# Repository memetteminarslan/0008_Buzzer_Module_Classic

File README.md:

# 0008_Buzzer_Module_Classic
You are seeing a large number of widely used Buzzer modules in electronic development kits. More information coming soon...

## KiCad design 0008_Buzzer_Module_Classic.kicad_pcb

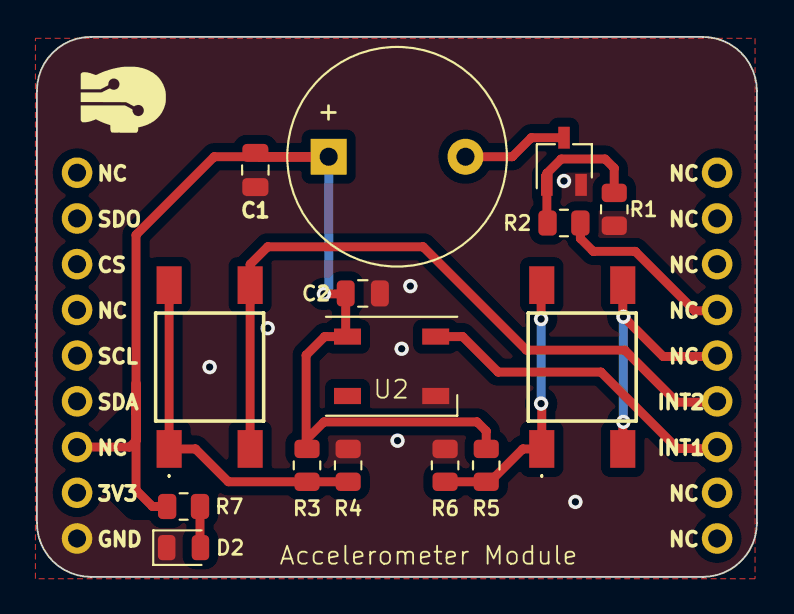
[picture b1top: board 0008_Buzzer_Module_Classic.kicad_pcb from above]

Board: 2 copper layers, 40.0 x 30.0 mm, 16 parts (0 on the bottom side), 11 nets.

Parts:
C1, C2: 0.1uF; C_0805_2012Metric
D1: WS2812B; LED_WS2812B_PLCC4_5.0x5.0mm_P3.2mm
D2: LED; LED_0805_2012Metric
Q1: SS8050-G; TSOT-23
R1: 10k; R_0805_2012Metric
R2: 4.7k; R_0805_2012Metric
R3, R4, R5, R6: 0r; R_0805_2012Metric
R7: 470r; R_0805_2012Metric
SW1, SW2: SW_MEC_5E; TS046665BK160SMT
U1: Buzzer; Buzzer_12x9.5RM7.6
U2: air_module

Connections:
+5V: C1.1, C2.1, D1.1 (VDD), R3.1, R5.1, R7.1, U1.1 (-), U2.7 (5V)
DIN: D1.4 (DIN), U2.12 (GPIO)
GND: C1.2, C2.2, D1.3 (VSS), D2.1 (K), Q1.2 (E), R1.1, R4.1, R6.1, U2.9 (GND)
GPIO_01: SW1.3 (K), SW1.4 (A), U2.13 (GPIO)
GPIO_02: SW2.3 (K), SW2.4 (A), U2.14 (GPIO)
unnamed: D2.2 (A), R7.2
unnamed: Q1.1 (B), R1.2, R2.1
unnamed: Q1.3 (C), U1.2 (+)
unnamed: R3.2, R4.2, SW1.1, SW1.2
unnamed: R5.2, R6.2, SW2.1, SW2.2
SIG: R2.2, U2.15 (GPIO)
